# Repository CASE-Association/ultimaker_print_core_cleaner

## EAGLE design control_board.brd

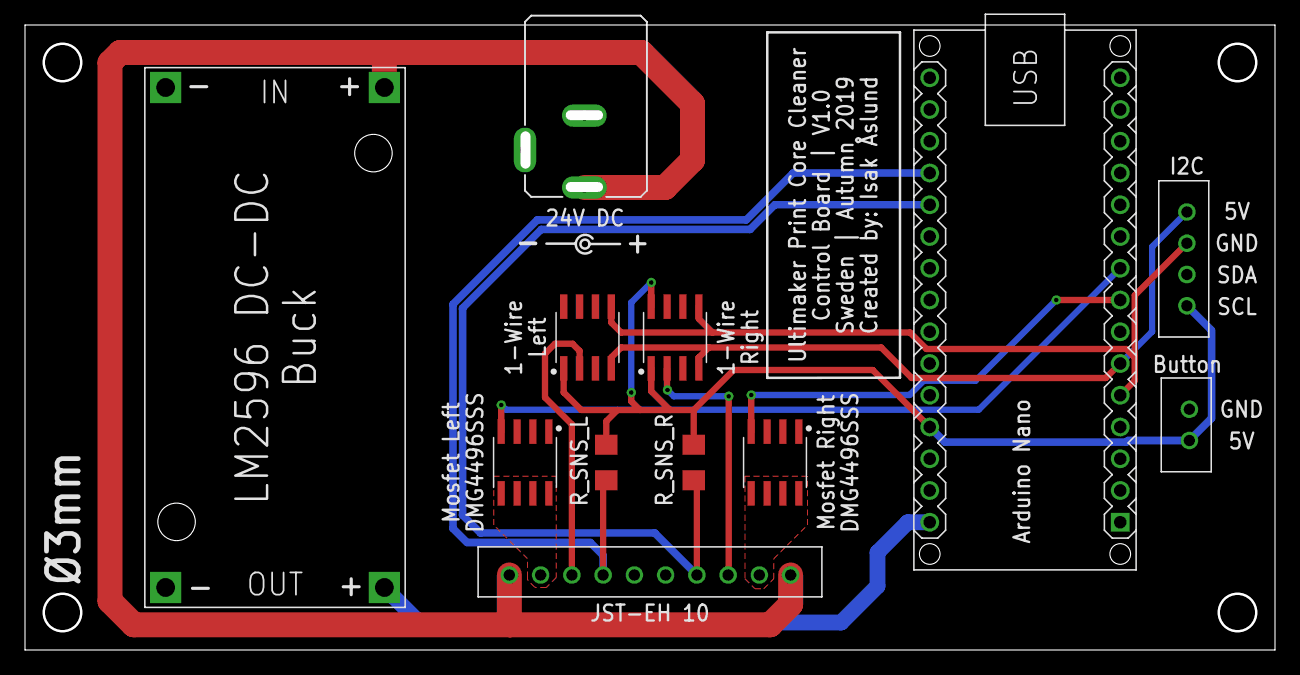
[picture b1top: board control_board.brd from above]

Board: 2 copper layers, 99.2 x 49.2 mm, 12 parts (0 on the bottom side), 14 nets.

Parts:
BUTTON: EH_B2B-EH; B2B-EH
CON1: EH_B10B-EH; B10B-EH
DC_JACK_24V: WE_694106301002
DS2482-100_L: Left; SOIC127P600X175-8N
DS2482-100_R: Right; SOIC127P600X175-8N
I2C: EH_B4B-EH; B4B-EH
M1: ARDUINO-NANO-3.0
R_SNS_L: 120Ω; R1206
R_SNS_R: 120Ω; R1206
U$1, U$2: DMG4496SSS; SOIC127P600X175-8N
U$5: DC-DC-STEP-DOWN-LM2596

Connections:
5V: BUTTON.1, DS2482-100_L.1, DS2482-100_R.1, DS2482-100_R.8, I2C.1, M1.J2.4, R_SNS_L.2, R_SNS_R.2
12V: M1.J2.1, U$5.OUT+
24V: CON1.1, CON1.10, DC_JACK_24V.1, U$5.IN+
DATA_L: CON1.3, DS2482-100_L.2
DATA_R: CON1.8, DS2482-100_R.2
GND: BUTTON.2, CON1.5, CON1.6, DC_JACK_24V.2, DC_JACK_24V.3, DS2482-100_L.3, DS2482-100_L.7, DS2482-100_L.8, DS2482-100_R.3, DS2482-100_R.7, I2C.2, M1.J1.4, M1.J2.2, U$1.1, U$1.2, U$1.3, U$2.1, U$2.2, U$2.3, U$5.IN-, U$5.OUT-
HEATER_2_L: CON1.2, U$1.5, U$1.6, U$1.7, U$1.8
HEATER_2_R: CON1.9, U$2.5, U$2.6, U$2.7, U$2.8
PT100_L: CON1.4, M1.J2.12, R_SNS_L.1
PT100_R: CON1.7, M1.J2.11, R_SNS_R.1
PWM_L: M1.J1.9, U$1.4
PWM_R: M1.J1.8, U$2.4
SCL: DS2482-100_L.4, DS2482-100_R.4, I2C.4, M1.J1.6
SDA: DS2482-100_L.5, DS2482-100_R.5, I2C.3, M1.J1.5

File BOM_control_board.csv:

Qty;Value;Device;Package;Parts;Description;VENDOR;Link
2;120;R1206;R1206;R_SNS_L, R_SNS_R;Standard Chip RESISTOR 1206 (3216 Metric);mouser;https://www.mouser.se/ProductDetail/Vishay-Dale/RCS1206120RF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
1;ARDUINO-NANO-3.0;ARDUINO-NANO-3.0;ARDUINO-NANO-3.0;M1;Arduino Nano 3.0 and compatible devices;case;-
1;DC-DC-STEP-DOWN-LM2596;DC-DC-STEP-DOWN-LM2596;DC-DC-STEP-DOWN-LM2596;U$5;DC/DC Step-Down Regulator based on LM2596-ADJ chip;case;-
2;DMG4496SSS;DMG4496SSS;SOIC127P600X175-8N;U$1, U$2;N-Channel Mosfetfor medium currents.;mouser;https://www.mouser.se/ProductDetail/Diodes-Incorporated/DMG4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
2;DS2482-100;DS2482-100;SOIC127P600X175-8N;DS2482-100_L, DS2482-100_R;DS2482-100;mouser;https://www.mouser.se/ProductDetail/Maxim-Integrated/DS2482S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
1;EH_B10B-EH;EH_B10B-EH;B10B-EH;CON1;JST EH Connector, through hole, 10 pin, top entry;case;
1;EH_B2B-EH;EH_B2B-EH;B2B-EH;BUTTON;JST EH Connector, through hole, 2 pin, top entry;case;
1;EH_B4B-EH;EH_B4B-EH;B4B-EH;I2C;JST EH Connector, through hole, 4 pin, top entry;case;
1;WE_694106301002;WE_694106301002;WE_694106301002;DC_JACK_24V;WE 694106301002, DC Power Jack;mouser;https://www.mouser.se/ProductDetail/Wurth-Elektronik/6941063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
;;;;;;;
;;;;;;;
;;;;;;;
;;;;;;;
;;;;;;;
;;;;;;;
;;;;;;;

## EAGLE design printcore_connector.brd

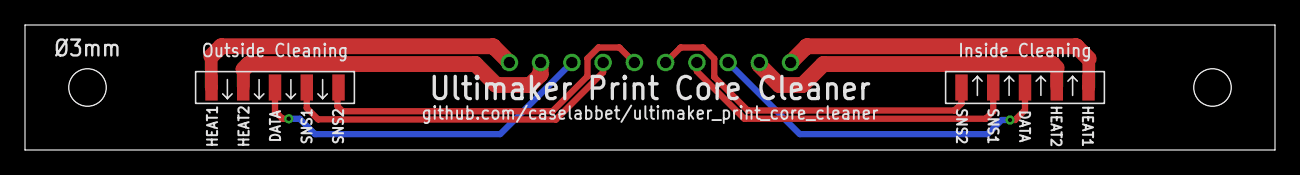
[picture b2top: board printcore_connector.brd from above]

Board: 2 copper layers, 99.9 x 9.9 mm, 3 parts (1 on the bottom side), 10 nets.

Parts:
CONNECTOR: EH_10_Side; S10B-EH
U$1, U$3: ULTIMAKER_PRINTCORE_CONNNECTOR; ULTIMAKER_PRINTCORE_CONNECTOR

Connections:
DATA_L: CONNECTOR.3, U$1.DATA
DATA_R: CONNECTOR.8, U$3.DATA
HEATER_1_L: CONNECTOR.1, U$1.HEATER@1
HEATER_1_R: CONNECTOR.10, U$3.HEATER@1
HEATER_2_L: CONNECTOR.2, U$1.HEATER@2
HEATER_2_R: CONNECTOR.9, U$3.HEATER@2
PT100_1_L: CONNECTOR.4, U$1.PT100@1
PT100_1_R: CONNECTOR.7, U$3.PT100@1
PT100_2_L: CONNECTOR.5, U$1.PT100@2
PT100_2_R: CONNECTOR.6, U$3.PT100@2

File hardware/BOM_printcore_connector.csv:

Qty;Value;Device;Package;Parts;Description;Vendor;Link
1;EH_10_Side;EH_S10B-EH;S10B-EH;CONNECTOR;JST EH Connector, through hole, 10 pin, side entry;rs components;https://se.rs-online.com/web/p/pcb-headers/5151377/
25;ULTIMAKER_PRINTCORE_CONNNECTOR;ULTIMAKER_PRINTCORE_CONNNECTOR;ULTIMAKER_PRINTCORE_CONNECTOR;U$1, U$3;Uses spring fingers 1.8H;mouser;https://www.mouser.se/ProductDetail/TE-Connectivity-AMP/2306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

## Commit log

2019-09-16 Silcscreen and 3D packages update
2019-09-16 Image and video
2019-09-18 Schematic for controlboard
2019-09-22 Final tweaks before production
2019-09-24 BOM update
2019-10-02 Folder structure update
2019-10-02 Create gitignore
2019-10-02 software structure setup
2019-10-02 .gitignore fix
2020-01-02 Program init
